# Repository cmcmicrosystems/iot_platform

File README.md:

# Compact BLE IoT Sensor Node
This IoT reference design is a compact BLE sensor node that features:
- Bluetooth Low Energy (BLE) wireless connectivity
- Array of real-time sensors
- Direct smartphone/tablet connectivity
- Coin cell battery for long life operation
- Small form factor
- JTAG programming access

The BLE SoC integrates an ARM Cortex-M3 to
control the wireless transceiver and interface with
the sensors. This design combines an ambient light
sensor, a temperature sensor, and an accelerometer
to enable applications such as building automation,
industrial equipment monitoring, etc.

A software interface app to display and log data is
included, and can be readily installed on any
Android system with BLE capabilities. This app
can communicate with and configure any sensor
node within the communications radius. The app
also provides estimates of the signal strength and
remaining battery lifetime for each sensor node.

This compact BLE sensor node can be used in
applications including:

- Real time sensing of ambient light and temperature for environmental monitoring and control
- HVAC systems and building automation
- Shock, vibration, and temperature monitoring of industrial equipment
- Theft, temperature monitoring of storage/shipping containers

This IoT Platform consists of:
- PCB design files for the KiCad v5.1.9 design environment.
- Source code and binary format firmware
- Android mobile app for data logging via smart phone

This project is provided as-is. Working samples (Alpha version) were created and tested successfully.

Prevents versions can be retreived by selecting the appropriate tag on Github at github.com/cmcmicrosystems/iot_platform

Versions:

Beta_HW_SW_Supported: Supported Hardware and Software for battery operation.  Manufactured 45 prototypes. aka SwiftMote IoT2021A

Beta : Current KiCAD v5.1.9. In manufacturing.  Changes made to sensors and crystals in BoM due to covid chip shortages.  New firmware for TMP100 temperature sensor (replacement for SI7051 in alpha).  Manufacturing information included.

Alpha : Initial version in Mentor Graphics PADS.  tested on a PCB, functional.

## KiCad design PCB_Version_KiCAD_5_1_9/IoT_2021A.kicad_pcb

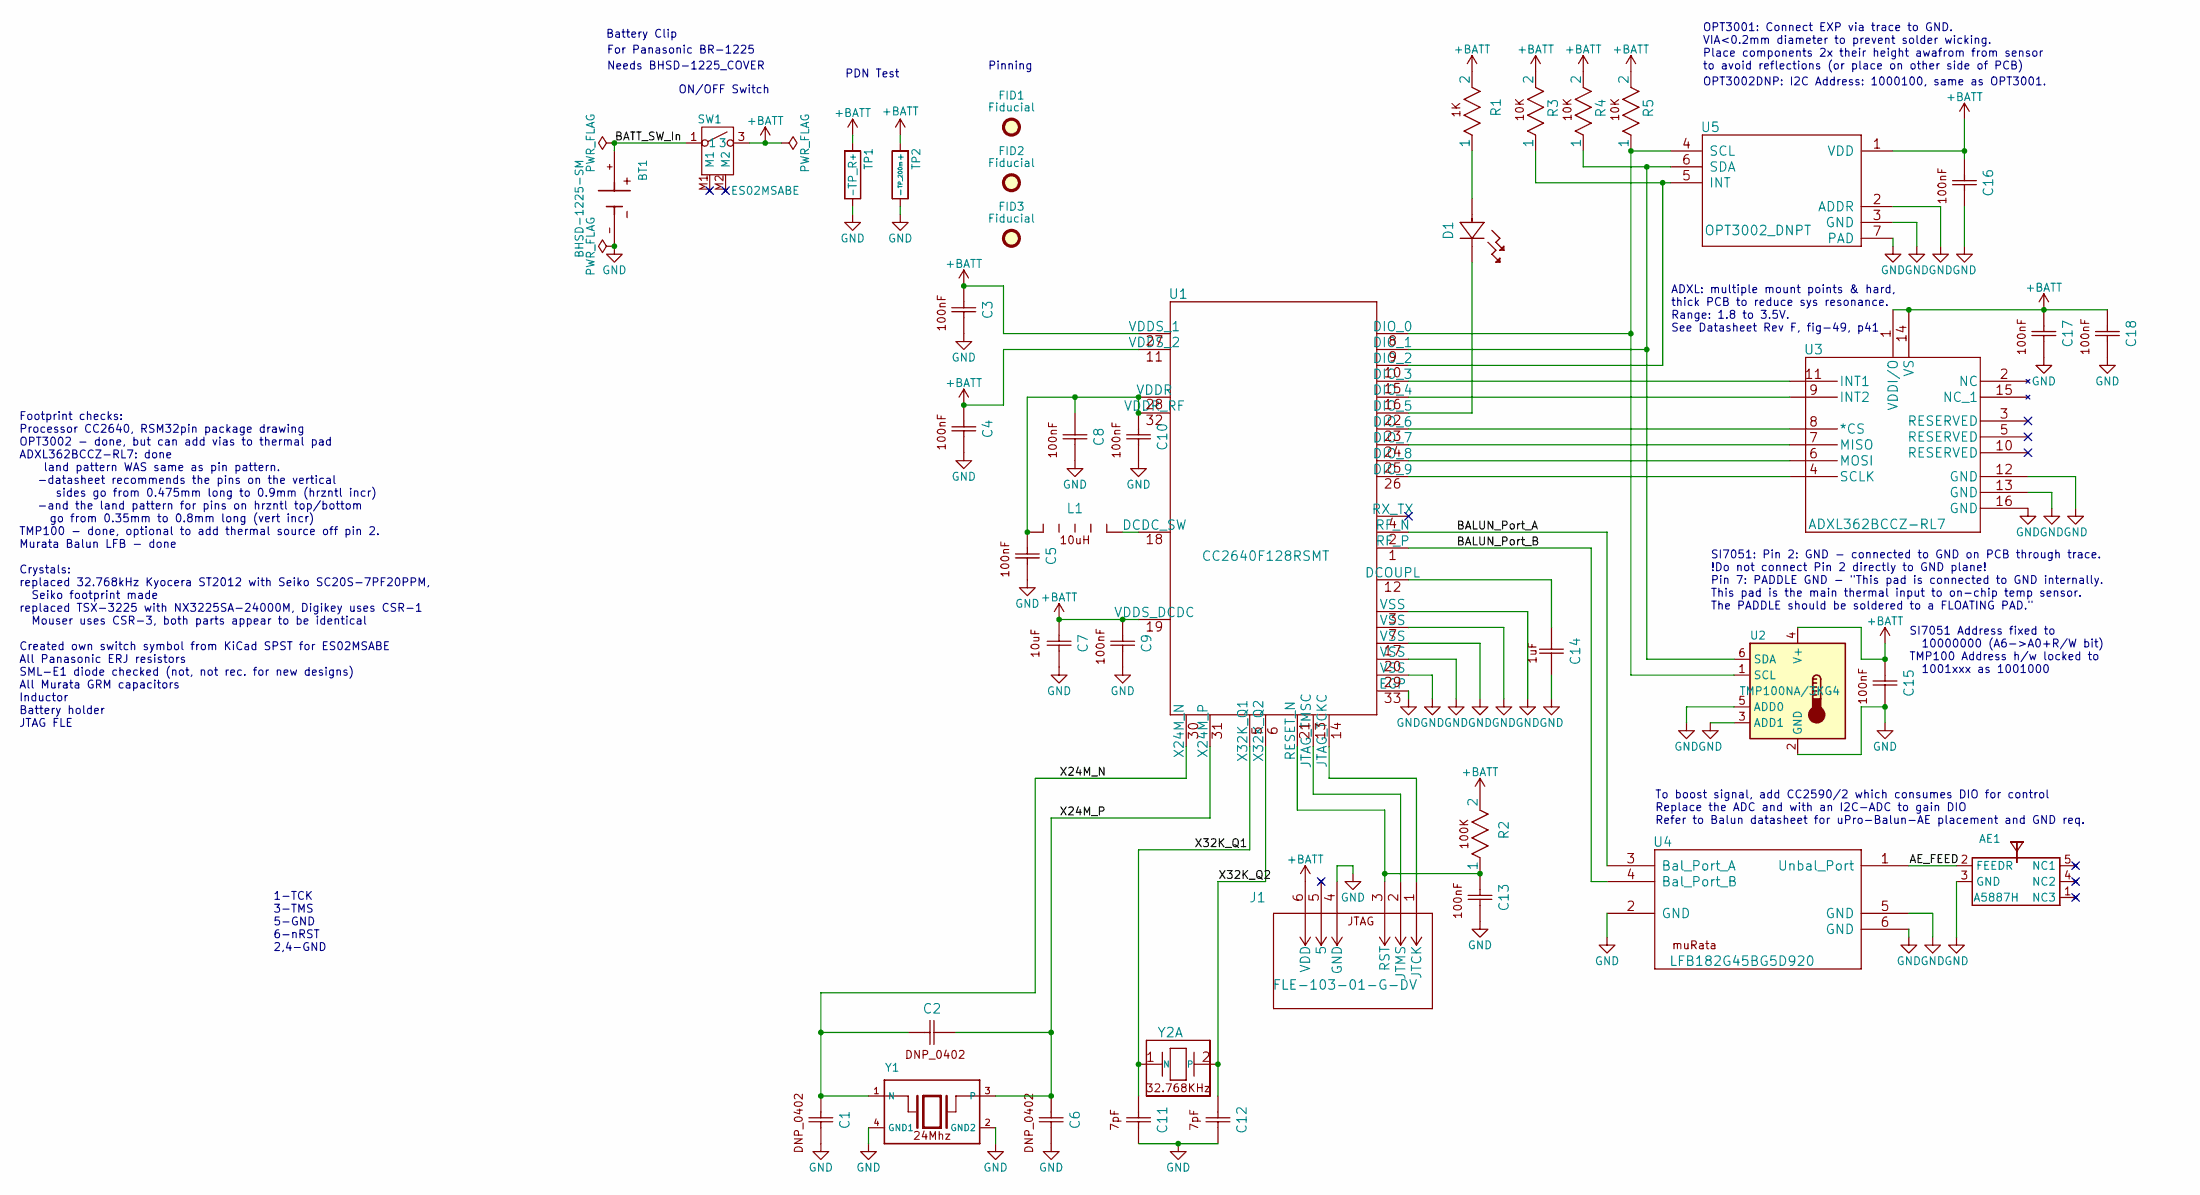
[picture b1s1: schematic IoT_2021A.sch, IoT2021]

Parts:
AE1: A5887H; RUFA_A5887H_right
BT1: BHSD-1225-SM; BAT_BHSD-1225-SM; PARTREV E
C1, C2, C6: GRM155R70J104KA01D_DNP; GRM155R70J104KA01D
C3, C4, C5, C8, C9, C10, C13, C15, C16, C17, C18: GRM155R70J104KA01D
C7: GRM188R60J106ME47D
C11, C12: GRM1555C1H7R0BA01D
C14: CL05A105KO5NNNC
D1: SMLE12WBC7W1
FID1, FID2, FID3: Fiducial; FID_45mil_NPTH
J1: FLE-103-01-G-DV
L1: CKS2125100M-T
R1: ERJ-2RKF1001X
R2: ERJ-2GEJ104X
R3, R4, R5: ERJ-2GEJ103X
SW1: ES02MSABE; SPST_ES02MSABE_jm
TP1: TP_R
TP2: TP_200m
U1: CC2640F128RSMT
U2: TMP100NA/3KG4; SOT-23-6
U3: ADXL362BCCZ-RL7
U4: LFB182G45BG5D920; Murata_SMD_6_balun
U5: OPT3002_DNPT; OPT3002DNPT_6_USON_SON65P200X200X65-7N
Y1: NX3225SA-24.000M-STD-CSR-1; NX3225SA_STD_CSR; PARTREV N/A
Y2: SC20S-7PF20PPM; SC20S_7PF20PPM_footprint

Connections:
+BATT: C3.1, C4.1, C7.1, C9.1, C15.1, C16.1, C17.1, C18.1, J1.6 (VDD), R1.2, R2.2, R3.2, R4.2, R5.2, SW1.3, TP1.1 (+), TP2.1 (+), U1.11 (VDDS_2), U1.19 (VDDS_DCDC), U1.27 (VDDS_1), U2.4 (V+), U3.1 (VDDI/O), U3.14 (VS), U5.1 (VDD)
/AE_FEED: AE1.2 (FEEDR), U4.1 (Unbal_Port)
/BALUN_Port_A: U1.2 (RF_N), U4.3 (Bal_Port_A)
/BALUN_Port_B: U1.1 (RF_P), U4.4 (Bal_Port_B)
/BATT_SW_In: BT1.+, SW1.1
/X24M_N: C1.1, C2.1, U1.30 (X24M_N), Y1.1 (N)
/X24M_P: C2.2, C6.1, U1.31 (X24M_P), Y1.3
/X32K_Q1: C11.1, U1.5 (X32K_Q1), Y2.1 (N)
/X32K_Q2: C12.1, U1.6 (X32K_Q2), Y2.2
GND: AE1.3 (GND), BT1.-, C1.2, C3.2, C4.2, C5.2, C6.2, C7.2, C8.2, C9.2, C10.2, C11.2, C12.2, C13.2, C14.2, C15.2, C16.2, C17.2, C18.2, J1.4 (GND), TP1.2 (-), TP2.2 (-), U1.3 (VSS), U1.7 (VSS), U1.17 (VSS), U1.20 (VSS), U1.29 (VSS), U1.33 (EGP), U2.2 (GND), U2.3 (ADD1), U2.5 (ADD0), U3.12 (GND), U3.13 (GND), U3.16 (GND), U4.2 (GND), U4.5 (GND), U4.6 (GND), U5.2 (ADDR), U5.3 (GND), U5.7 (PAD), Y1.2 (GND2), Y1.4 (GND1)
unnamed: C5.1, C8.1, C10.1, L1.2, U1.28 (VDDR), U1.32 (VDDR_RF)
unnamed: C13.1, J1.3 (RST), R2.1, U1.21 (RESET_N)
unnamed: C14.1, U1.12 (DCOUPL)
unnamed: D1.1, U1.22 (DIO_5)
unnamed: D1.2, R1.1
unnamed: J1.1 (JTCK), U1.14 (JTAG_TCKC)
unnamed: J1.2 (JTMS), U1.13 (JTAG_TMSC)
unnamed: L1.1, U1.18 (DCDC_SW)
unnamed: R3.1, U1.10 (DIO_2), U5.5 (INT)
unnamed: R4.1, U1.9 (DIO_1), U2.6 (SDA), U5.6 (SDA)
unnamed: R5.1, U1.8 (DIO_0), U2.1 (SCL), U5.4 (SCL)
unnamed: U1.15 (DIO_3), U3.11 (INT1)
unnamed: U1.16 (DIO_4), U3.9 (INT2)
unnamed: U1.23 (DIO_6), U3.8 (*CS)
unnamed: U1.24 (DIO_7), U3.7 (MISO)
unnamed: U1.25 (DIO_8), U3.6 (MOSI)
unnamed: U1.26 (DIO_9), U3.4 (SCLK)

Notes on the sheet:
Battery Clip
For Panasonic BR-1225
Needs BHSD-1225_COVER
PDN Test
ON/OFF Switch
To boost signal, add CC2590/2 which consumes DIO for control Replace the ADC and with an I2C-ADC to gain DIO Refer to Balun datasheet for uPro-Balun-AE placement and GND req.
OPT3001: Connect EXP via trace to GND. VIA<0.2mm diameter to prevent solder wicking. Place components 2x their height awafrom from sensor to avoid reflections (or place on other side of PCB)
ADXL: multiple mount points & hard, thick PCB to reduce sys resonance. Range: 1.8 to 3.5V. See Datasheet Rev F, fig-49, p41
SI7051: Pin 2: GND - connected to GND on PCB through trace. !Do not connect Pin 2 directly to GND plane! Pin 7: PADDLE GND - "This pad is connected to GND internally. This pad is the main thermal input to on-chip temp sensor. The PADDLE should be soldered to a FLOATING PAD."
OPT3002DNP: I2C Address: 1000100, same as OPT3001.
SI7051 Address fixed to 10000000 (A6->A0+R/W bit) TMP100 Address h/w locked to 1001xxx as 1001000
1-TCK 3-TMS 5-GND 6-nRST 2,4-GND
Pinning
Footprint checks: Processor CC2640, RSM32pin package drawing OPT3002 - done, but can add vias to thermal pad ADXL362BCCZ-RL7: done land pattern WAS same as pin pattern. -datasheet recommends the pins on the vertical sides go from 0.475mm long to 0.9mm (hrzntl incr) -and the land pattern for pins on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

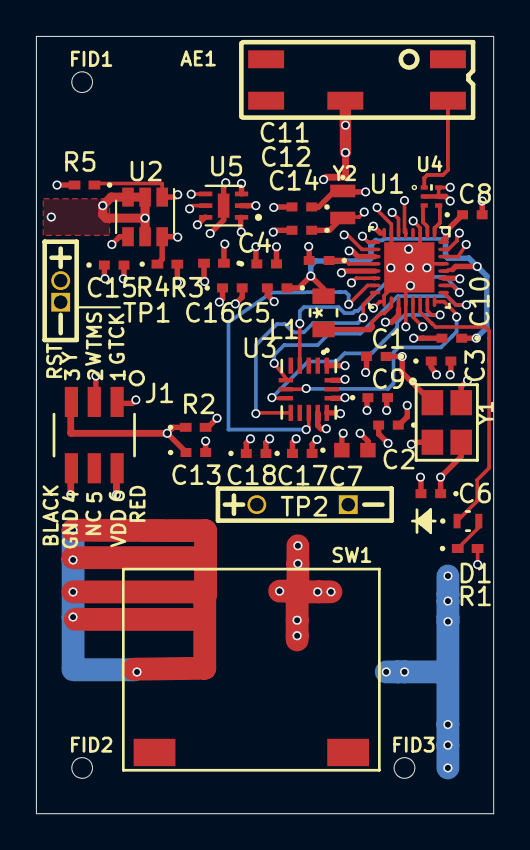
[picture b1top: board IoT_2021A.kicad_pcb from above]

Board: 6 copper layers, 25.4 x 43.2 mm, 41 parts (1 on the bottom side), 27 nets.

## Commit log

2020-05-06 HPS source files added
2020-05-06 A file was deleted
2020-05-06 Image added
2021-06-30 Beta Version, KiCad 5.1.9, hardware only, firmware to come
2021-11-03 update the firmware code with intervals suitable for battery operation
2021-11-08 BETA Release, Hardware and Software Supported, Battery Operation. SwiftMote IoT2021A.
2021-12-15 Add information about the firmware

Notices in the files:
parts and their libraries:
Copyright 2016 Accelerated Designs. All rights reserved.
